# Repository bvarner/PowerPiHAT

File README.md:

# PowerPiHAT
A Raspberry Pi HAT for building a whole-house electricity monitor using PZCT-02 split core current transformers.

## Design Decisions
* Use an inexpensive split-core CT capable of 100A, that can be clipped onto the mains in my electrical panel.
* Allow for easy connection of the CTs to the device.
* Produce a spec-compliant HAT.
    * Safely back-power the Raspberry Pi from the HAT.
    * Proper cutouts, clearances, etc.
* Use an inexpensive ADS1115 module to reduce overall part cost. (It's cheaper to buy a breakout module than it is to buy the chips in low quantity)
    * GY-ADS1115 (Available from ebay, aliexpress, etc.)
    * Adafruit ADS1115. Both are pin-compatible, and there are mount holes for each module on the board.

## The Board
You can manufacture the board at home, using dual-sided 2-oz copper-clad board. Important: The traces for the analog input are sized assuming 2oz copper.

I've optimized trace spacing for what I've been capable of producing at home using the 'laser-printer hot-transfer' method to mask prior to chemical etching.
There are also extraneous vias to breakout header pins in case soldering both sides of the pin is problematic (no through-hole plating).

The footprints of the SMT components could be smaller for mass production, but I chose the sizes based on what I've been able to hand-solder with an inexpensive 'hobbiest' 25watt soldering iron with a blade tip.

Contrary to the HAT spec, the mounting holes are not defined as non-plated through-hole in the current repository. Since I'm hand-manufacturing these boards, I need to have a precise drill location. KiCad doesn't seem to emit drill markers to the etch layers unless the hole is plated through-hole. So, I've set those as plated, and will drill the entire pad away.

## Sourcing Parts

Estimated total cost fo the build, with more parts than you need (volume pricing on imports), comes to around **$65** -- including the RaspberryPi!

### Import Parts / Supplies for the PCB

| Quantity | Part | Est. Cost Each | Est. Build Cost |
| -------- | ---- | --------------:| ---------------:|
| 4        | [PZCT-02 CT](https://www.aliexpress.com/wholesale?SearchText=PZCT-02) | ~$3.75 | $16 |
| 1        | [GY-ADS1115](https://www.aliexpress.com/wholesale?SearchText=ADS1115) | ~$1.60 | $2 |
| 1        | [Double Sided Copper Clad Board](https://www.aliexpress.com/wholesale?SearchText=double+side+copper+clad) | ~$0.60 | ? |
| 1        | [Raspberry Pi Model 3 A+](https://www.adafruit.com/product/4027) | ~$25 | $32 | 
| 1        | [DC-092 Barrel Jack](https://www.aliexpress.com/item/Free-shipping-20pcs-lot-DC-connector-tablet-female-DC-power-jack-SMD-DIP-PCB-mounting-DC/32684566314.html) | ~$0.16 | $2 |
| 4        | [3.5mm Mono Audio Jacks - SMT](https://www.aliexpress.com/item/Promotion-5-Pcs-5-Pin-3-5mm-Audio-Mono-Jack-Socket-PCB-Panel-Mount-for-Headphone/32622989834.html) | ~$0.15 | $1 |
| 4        | [3.5mm Mono Audio Plugs](https://www.aliexpress.com/item/10Pcs-3-5MM-Headphone-Plug-2-Pole-Mono-Audio-Video-Welding-Line-For-Headphone-Socket/32789017811.html) | ~$0.11 | $1 |

### DigiKey BOM
As of 5/21/2019, the estimated BOM cost is ~$10.

```
﻿"Manufacturer Part Number"	"Digi-Key Part Number"	"Customer Reference"	"Reference Designator"	"Quantity"	"Unit Price"	"Description"
"DMG2305UX-13"	"DMG2305UX-13DICT-ND"	""	"Q1"	"1"	"0.45000"	"MOSFET P-CH 20V 4.2A SOT23"
"DMMT5401-7-F"	"DMMT5401-FDICT-ND"	""	"Q2"	"1"	"0.45000"	"TRANS 2PNP 150V 0.2A SOT26"
"RNCF0805DTE10K0"	"RNCF0805DTE10K0CT-ND"	""	""	"10"	"0.14000"	"RES 10K OHM 0.5% 1/8W 0805"
"RNCF0805DTE47K0"	"RNCF0805DTE47K0CT-ND"	""	"R24"	"1"	"0.15000"	"RES 47K OHM 0.5% 1/8W 0805"
"CAT24C32WI-GT3"	"CAT24C32WI-GT3CT-ND"	""	"U2"	"1"	"0.20000"	"IC EEPROM 32K I2C 1MHZ 8SOIC"
"RNCF0805DTE3K90"	"RNCF0805DTE3K90CT-ND"	""	""	"2"	"0.15000"	"RES 3.9K OHM 0.5% 1/8W 0805"
"CRGP2010F18R"	"A130639CT-ND"	""	""	"4"	"0.43000"	"CRGP 2010 18R 1%"
"CL21A106KPFNNNE"	"1276-1052-1-ND"	""	""	"4"	"0.13000"	"CAP CER 10UF 10V X5R 0805"
"SSQ-110-03-T-S"	"SAM1206-10-ND"	""	"J1"	"1"	"1.20000"	"CONN RCPT 10POS 0.1 TIN PCB"
"SSW-120-01-T-D"	"SAM1212-20-ND"	""	"J3"	"1"	"2.90000"	"CONN RCPT 40POS 0.1 TIN PCB"
```

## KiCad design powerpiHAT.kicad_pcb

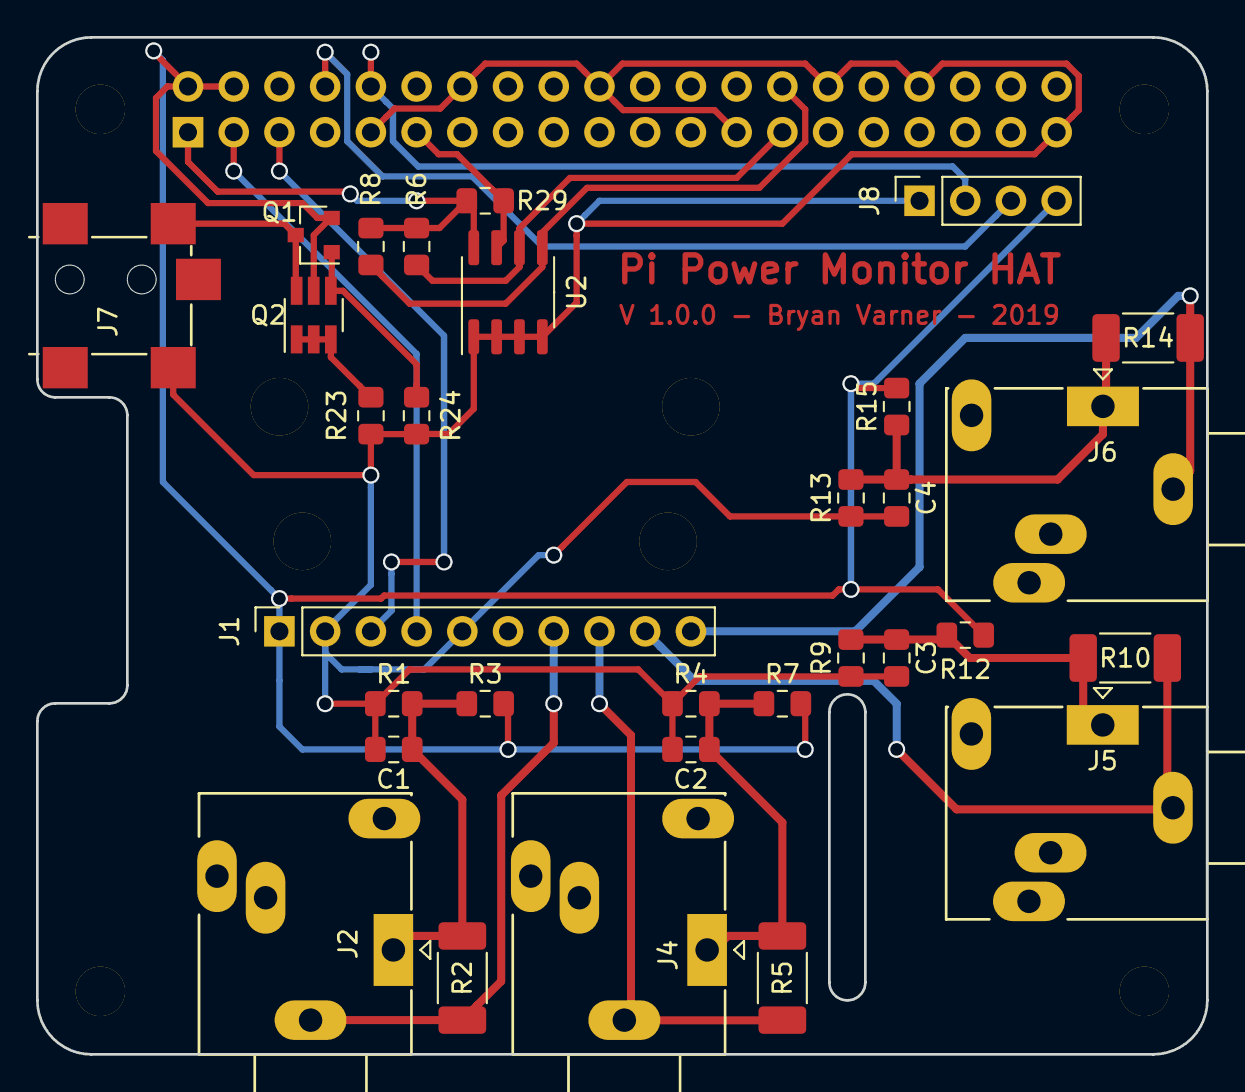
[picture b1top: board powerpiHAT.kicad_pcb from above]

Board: 2 copper layers, 65.0 x 56.5 mm, 40 parts (1 on the bottom side), 21 nets.

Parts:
C1, C2, C3, C4: 10uF; C_0805_2012Metric_Pad1.15x1.40mm_HandSolder
H1, H2, H3, H4: 3mm_Mounting_Hole; MountingHole_2.7mm_M2.5
H5, H6, H7, H8: 3mm_Mounting_Hole; MountingHole_3.2mm_M3_DIN965
J1: Conn_01x10; PinSocket_1x10_P2.54mm_Vertical
J2, J4, J5, J6: AudioJack2_Dual_Ground_Switche; Jack_3.5mm_Ledino_KB3SPRS_Horizontal
J3: 40HAT; PinSocket_2x20_P2.54mm_Vertical
J7: Barrel_Jack; BarrellJack-DC-902_SMT_Horizontal
J8: Conn_01x04; PinSocket_1x04_P2.54mm_Vertical
Q1: DMG2305UX; SOT-23
Q2: DMMT5401; SOT-23-6_Handsoldering
R1, R3, R4, R7, R9, R12, R13, R15, R23, R29: 10K; R_0805_2012Metric_Pad1.15x1.40mm_HandSolder
R2, R5, R10, R14: 18; R_2010_5025Metric_Pad1.52x2.65mm_HandSolder
R6, R8: 3.9K; R_0805_2012Metric_Pad1.15x1.40mm_HandSolder
R24: 47K; R_0805_2012Metric_Pad1.15x1.40mm_HandSolder
U2: CAT24C32; SOIC-8_3.9x4.9mm_P1.27mm

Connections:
/ADS_A0: J1.7, J2.S, R2.1
/ADS_A1: J1.8, J4.S, R5.1
/ADS_A2: J1.9, J5.S, R10.1
/ADS_A3: J1.10, J6.S, R14.1
/BCM_2: J1.4, J3.3
/BCM_3: J1.3, J3.5
/ID_SC_EEPROM: J3.28, R8.2, U2.5
/ID_SD_EEPROM: J3.27, R6.2, U2.6
/P3V3_HAT: J3.1, R6.1, R8.1, R29.1, U2.8
/P5V: J7.1, Q1.3, Q2.6
/P5V_HAT: J1.1, J3.2, J3.4, J8.4, Q1.2, Q2.5, R3.2, R7.2, R12.2, R15.2
/PI_UART_RXD: J3.10, J8.2
/PI_UART_TXD: J3.8, J8.3
/WP_EEPROM: J3.11, R29.2, U2.7
GND: C1.2, C2.2, C3.2, C4.2, J1.2, J1.5, J3.9, J3.14, J3.20, J3.25, J3.30, J3.34, J3.39, J7.2, J8.1, R1.1, R4.1, R9.1, R13.1, R23.2, R24.2, U2.1, U2.2, U2.3, U2.4
unnamed: C1.1, J2.T, R1.2, R2.2, R3.1
unnamed: C2.1, J4.T, R4.2, R5.2, R7.1
unnamed: C3.1, J5.T, R9.2, R10.2, R12.1
unnamed: C4.1, J6.T, R13.2, R14.2, R15.1
unnamed: Q1.1, Q2.4, R24.1
unnamed: Q2.1, Q2.2, Q2.3, R23.1

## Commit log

2019-05-14 Initial checkin of the initial revision of hardware.
2019-05-21 Essentially, release 1.0.0 of the PowerPiHAT... we'll see if there's electrical changes necessary once we get a couple boards etched and populated.
2019-05-21 Updating the redme.
2019-05-21 Include the UART on a breakout header, for additional bits later.
2019-05-22 Breakout Header for 5v, Gnd, UART
2019-05-22 Board Margin.
2019-05-22 Mounting holes are now through-hole, so we get reference points for drilling (drill marks) by hand.
2019-05-22 Adding home_etch plots.
2019-05-23 Moved the I2C For the ADS to the proper lines.
2019-05-23 Mount positions for the adafruit module. I happen to have both types on-hand for testing.d
